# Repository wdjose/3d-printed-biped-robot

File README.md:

# 3D-Printed Biped Robot
This repository contains the 3D model and the source code for the 3D-printed biped robot presented in the conference: 

> [W. J. D. Jose and M. C. Ramos, "Development of a 3D-printed biped robot with distributed joint control," 2018 4th International Conference on Control, Automation and Robotics (ICCAR), Auckland, 2018, pp. 71-75.](https://ieeexplore.ieee.org/document/8384647/ "Development of a 3D-printed biped robot with distributed joint control")

The biped robot was designed from scratch: all mechanical, electronic, and control designs were built by the authors. 

Below are descriptions of the directories in the repository: 
1. 3D Model: This contains the SolidWorks parts and assemblies which was 3D-printed and laser cut. 
2. PCB Schematic and Layout: This contains EAGLE schematic and layout files for both the master and joint controllers. 
3. Joint Controller: This is the MPLAB X project used for motor control for the joint controller. 
4. Master Controller: This is the MPLAB X project used for motion control of the biped for the master controller. 

Additional details can be provided upon request. 

This project was developed at Electrical and Electronics Engineering Institute, University of the Philippines Diliman.

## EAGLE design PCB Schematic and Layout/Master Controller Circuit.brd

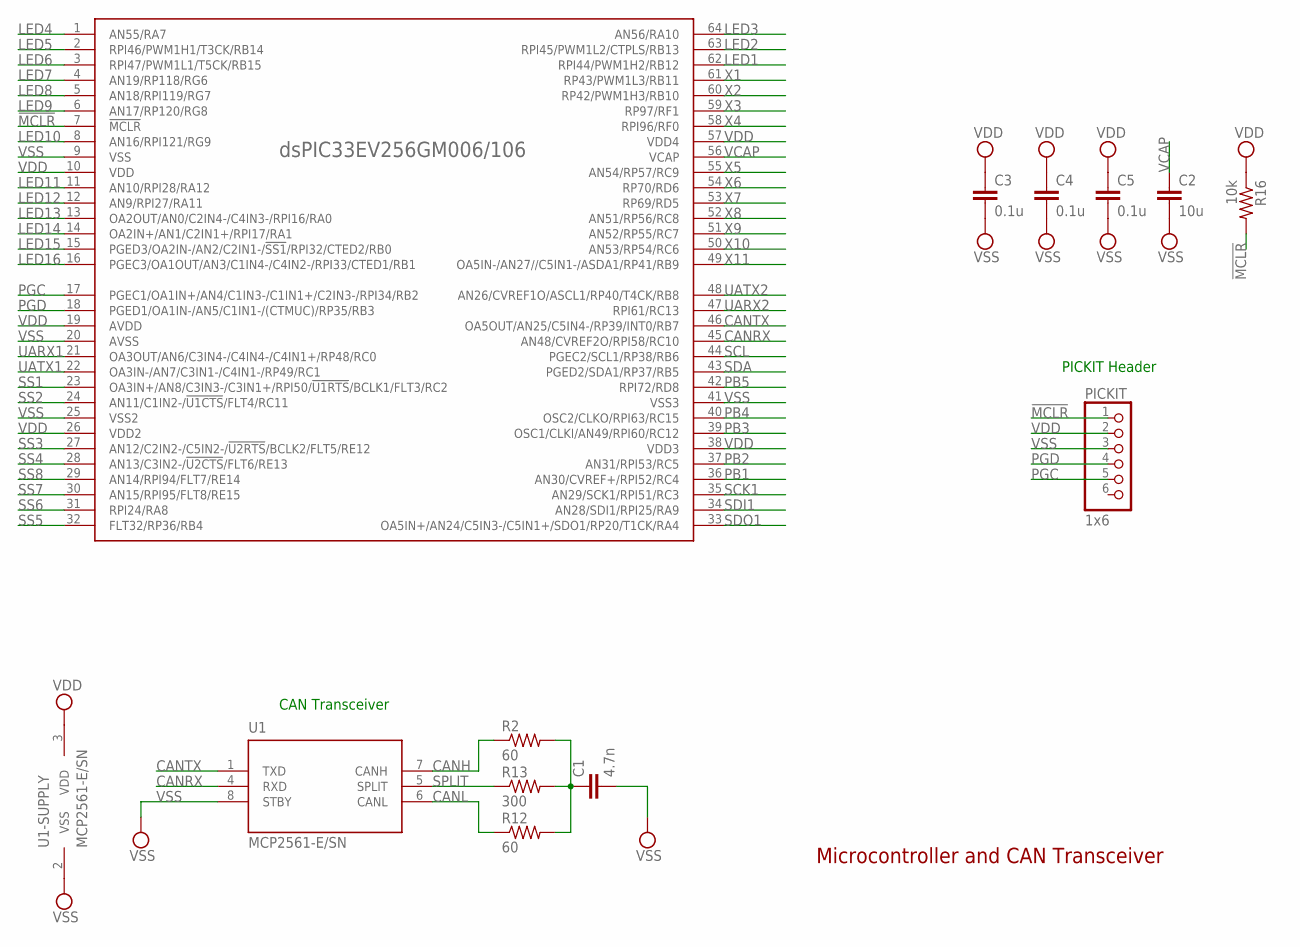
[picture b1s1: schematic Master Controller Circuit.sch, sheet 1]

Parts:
C1: 4.7n; C0805
C2: 10u; C0805
C3, C4, C5: 0.1u; C0805
PICKIT: 1x6; 1X06
R2, R12: 60; R0805
R13: 300; R0805
R16: 10k; R0805
U1: MCP2561-E/SN; SOIC-8
U$1: DSPIC33EV256GM106; TQFP64-10X10

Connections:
!MCLR: PICKIT.1, R16.2, U$1.7 (!MCLR); also elsewhere on the board
CANH: R2.1, U1.7 (CANH); also elsewhere on the board
CANL: R12.1, U1.6 (CANL); also elsewhere on the board
CANRX: U1.4 (RXD), U$1.45 (AN48/CVREF2O/RPI58/RC10)
CANTX: U1.1 (TXD), U$1.46 (OA5OUT/AN25/C5IN4-/RP39/INT0/RB7)
LED1: U$1.62 (RPI44/PWM1H2/RB12); also elsewhere on the board
LED2: U$1.63 (RPI45/PWM1L2/CTPLS/RB13); also elsewhere on the board
LED3: U$1.64 (AN56/RA10); also elsewhere on the board
LED4: U$1.1 (AN55/RA7); also elsewhere on the board
LED5: U$1.2 (RPI46/PWM1H1/T3CK/RB14); also elsewhere on the board
LED6: U$1.3 (RPI47/PWM1L1/T5CK/RB15); also elsewhere on the board
LED7: U$1.4 (AN19/RP118/RG6); also elsewhere on the board
LED8: U$1.5 (AN18/RPI119/RG7); also elsewhere on the board
LED9: U$1.6 (AN17/RP120/RG8); also elsewhere on the board
LED10: U$1.8 (AN16/RPI121/RG9); also elsewhere on the board
LED11: U$1.11 (AN10/RPI28/RA12); also elsewhere on the board
LED12: U$1.12 (AN9/RPI27/RA11); also elsewhere on the board
LED13: U$1.13 (OA2OUT/AN0/C2IN4-/C4IN3-/RPI16/RA0); also elsewhere on the board
LED14: U$1.14 (OA2IN+/AN1/C2IN1+/RPI17/RA1); also elsewhere on the board
LED15: U$1.15 (PGED3/OA2IN-/AN2/C2IN1-/!SS1!/RPI32/CTE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); also elsewhere on the board
LED16: U$1.16 (PGEC3/OA1OUT/AN3/C1IN4-/C4IN2-/RPI33/CT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); also elsewhere on the board
unnamed: C1.1, R2.2, R12.2, R13.2
PB1: U$1.36 (AN30/CVREF+/RPI52/RC4); also elsewhere on the board
PB2: U$1.37 (AN31/RPI53/RC5); also elsewhere on the board
PB3: U$1.39 (OSC1/CLKI/AN49/RPI60/RC12); also elsewhere on the board
PB4: U$1.40 (OSC2/CLKO/RPI63/RC15); also elsewhere on the board
PB5: U$1.42 (RPI72/RD8); also elsewhere on the board
PGC: PICKIT.5, U$1.17 (PGEC1/OA1IN+/AN4/C1IN3-/C1IN1+/C2IN3-/R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)
PGD: PICKIT.4, U$1.18 (PGED1/OA1IN-/AN5/C1IN1-/(CTMUC)/RP35/RB3)
SCK1: U$1.35 (AN29/SCK1/RPI51/RC3); also elsewhere on the board
SCL: U$1.44 (PGEC2/SCL1/RP38/RB6); also elsewhere on the board
SDA: U$1.43 (PGED2/SDA1/RP37/RB5); also elsewhere on the board
SDI1: U$1.34 (AN28/SDI1/RPI25/RA9); also elsewhere on the board
SDO1: U$1.33 (OA5IN+/AN24/C5IN3-/C5IN1+/SDO1/RP20/T1C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); also elsewhere on the board
SPLIT: R13.1, U1.5 (SPLIT)
SS1: U$1.23 (OA3IN+/AN8/C3IN3-/C3IN1+/RPI50/!U1RTS!/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); also elsewhere on the board
SS2: U$1.24 (AN11/C1IN2-/!U1CTS!/FLT4/RC11); also elsewhere on the board
SS3: U$1.27 (AN12/C2IN2-/C5IN2-/!U2RTS!/BCLK2/FLT5/R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); also elsewhere on the board
SS4: U$1.28 (AN13/C3IN2-/!U2CTS!/FLT6/RE13); also elsewhere on the board
SS5: U$1.32 (FLT32/RP36/RB4); also elsewhere on the board
SS6: U$1.31 (RPI24/RA8); also elsewhere on the board
SS7: U$1.30 (AN15/RPI95/FLT8/RE15); also elsewhere on the board
SS8: U$1.29 (AN14/RPI94/FLT7/RE14); also elsewhere on the board
UARX1: U$1.21 (OA3OUT/AN6/C3IN4-/C4IN4-/C4IN1+/RP48/RC0); also elsewhere on the board
UARX2: U$1.47 (RPI61/RC13); also elsewhere on the board
UATX1: U$1.22 (OA3IN-/AN7/C3IN1-/C4IN1-/RP49/RC1); also elsewhere on the board
UATX2: U$1.48 (AN26/CVREF1O/ASCL1/RP40/T4CK/RB8); also elsewhere on the board
VCAP: C2.1, U$1.56 (VCAP)
VDD: C3.1, C4.1, C5.1, PICKIT.2, R16.1, U1.3 (VDD), U$1.10 (VDD), U$1.19 (AVDD), U$1.26 (VDD2), U$1.38 (VDD3), U$1.57 (VDD4); also elsewhere on the board
VSS: C1.2, C2.2, C3.2, C4.2, C5.2, PICKIT.3, U1.2 (VSS), U1.8 (STBY), U$1.9 (VSS), U$1.20 (AVSS), U$1.25 (VSS2), U$1.41 (VSS3); also elsewhere on the board
X1: U$1.61 (RP43/PWM1L3/RB11); also elsewhere on the board
X2: U$1.60 (RP42/PWM1H3/RB10); also elsewhere on the board
X3: U$1.59 (RP97/RF1); also elsewhere on the board
X4: U$1.58 (RPI96/RF0); also elsewhere on the board
X5: U$1.55 (AN54/RP57/RC9); also elsewhere on the board
X6: U$1.54 (RP70/RD6); also elsewhere on the board
X7: U$1.53 (RP69/RD5); also elsewhere on the board
X8: U$1.52 (AN51/RP56/RC8); also elsewhere on the board
X9: U$1.51 (AN52/RP55/RC7); also elsewhere on the board
X10: U$1.50 (AN53/RP54/RC6); also elsewhere on the board
X11: U$1.49 (OA5IN-/AN27//C5IN1-/ASDA1/RP41/RB9); also elsewhere on the board

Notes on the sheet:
PICKIT Header
CAN Transceiver
Microcontroller and CAN Transceiver

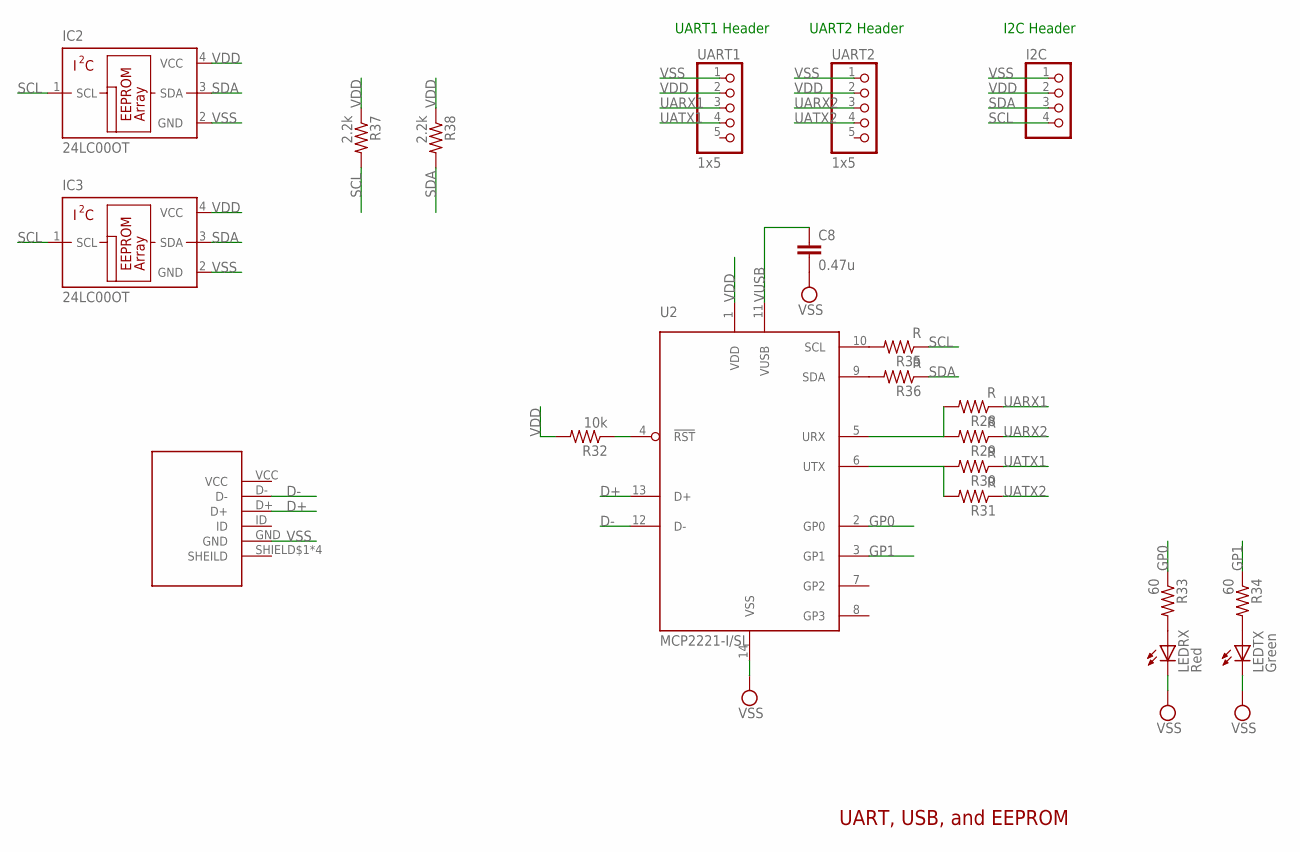
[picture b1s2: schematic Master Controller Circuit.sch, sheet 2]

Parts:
C8: 0.47u; C0805
I2C: PINHD-1X4; 1X04
IC2, IC3: 24LC00OT; SOT23-5L
J1: 10118193-0001LF
LEDRX: Red; CHIP-LED0805
LEDTX: Green; CHIP-LED0805
R28, R29, R30, R31, R35, R36: R; R0805
R32: 10k; R0805
R33, R34: 60; R0805
R37, R38: 2.2k; R0805
U2: MCP2221-I/SL; SOIC14
UART1, UART2: 1x5; 1X05

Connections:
D+: J1.D+, U2.13 (D+)
D-: J1.D-, U2.12 (D-)
GP0: R33.1, U2.2 (GP0)
GP1: R34.1, U2.3 (GP1)
unnamed: R28.2, R29.2, U2.5 (URX)
unnamed: R30.2, R31.2, U2.6 (UTX)
unnamed: R35.2, U2.10 (SCL)
unnamed: R36.2, U2.9 (SDA)
unnamed: R32.1, U2.4 (!RST)
unnamed: LEDRX.A, R33.2
unnamed: LEDTX.A, R34.2
SCL: I2C.4, IC2.1 (SCL), IC3.1 (SCL), R35.1, R37.2; also elsewhere on the board
SDA: I2C.3, IC2.3 (SDA), IC3.3 (SDA), R36.1, R38.2; also elsewhere on the board
UARX1: R28.1, UART1.3; also elsewhere on the board
UARX2: R29.1, UART2.3; also elsewhere on the board
UATX1: R30.1, UART1.4; also elsewhere on the board
UATX2: R31.1, UART2.4; also elsewhere on the board
VDD: I2C.2, IC2.4 (VCC), IC3.4 (VCC), R32.2, R37.1, R38.1, U2.1 (VDD), UART1.2, UART2.2; also elsewhere on the board
VSS: C8.2, I2C.1, IC2.2 (GND), IC3.2 (GND), J1.GND, LEDRX.C, LEDTX.C, U2.14 (VSS), UART1.1, UART2.1; also elsewhere on the board
VUSB: C8.1, U2.11 (VUSB)

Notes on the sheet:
UART, USB, and EEPROM
UART1 Header
UART2 Header
I2C Header

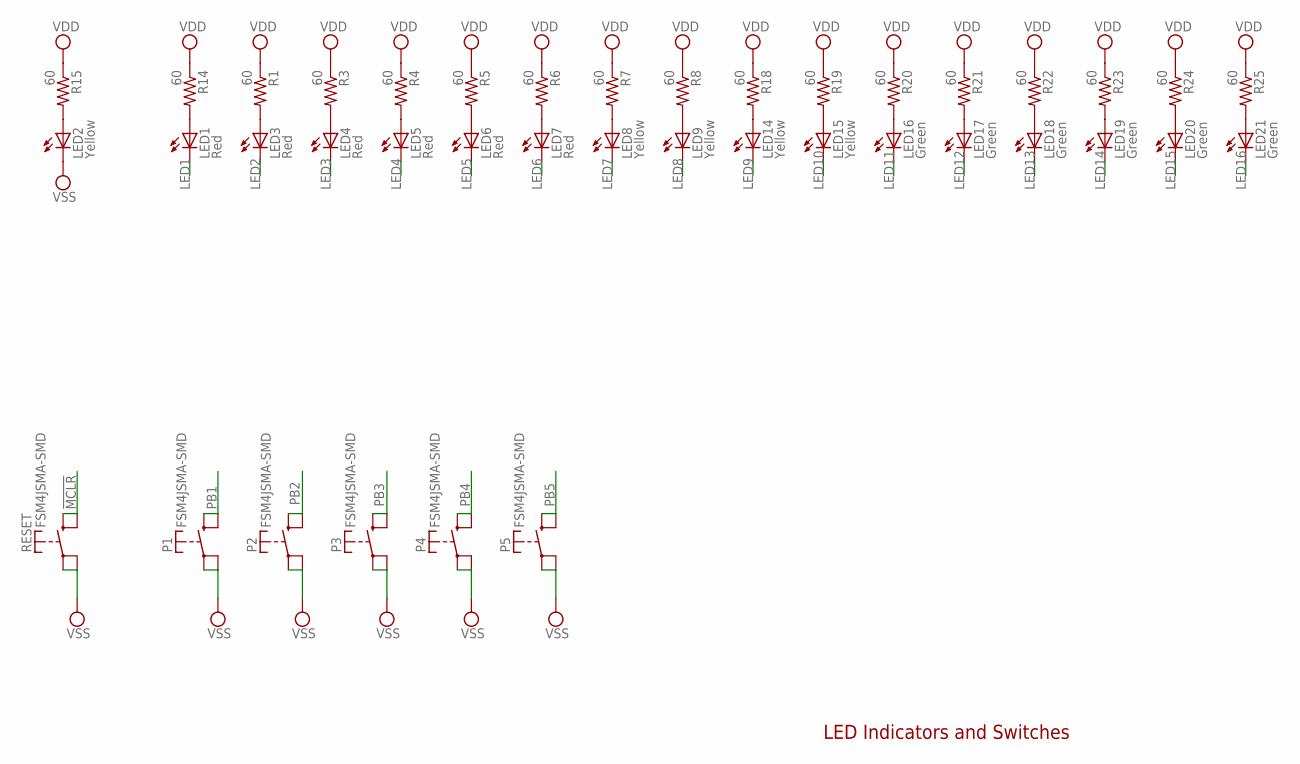
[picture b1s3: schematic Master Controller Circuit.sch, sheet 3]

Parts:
LED1, LED3, LED4, LED5, LED6, LED7: Red; CHIP-LED0805
LED2, LED8, LED9, LED14, LED15: Yellow; CHIP-LED0805
LED16, LED17, LED18, LED19, LED20, LED21: Green; CHIP-LED0805
P1, P2, P3, P4, P5: FSM4JSMA-SMD
R1, R3, R4, R5, R6, R7, R8, R14, R15, R18, R19, R20, R21, R22, R23, R24, R25: 60; R0805
RESET: FSM4JSMA-SMD

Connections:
!MCLR: RESET.P$3 (S), RESET.P$4 (S); also elsewhere on the board
LED1: LED1.C; also elsewhere on the board
LED2: LED3.C; also elsewhere on the board
LED3: LED4.C; also elsewhere on the board
LED4: LED5.C; also elsewhere on the board
LED5: LED6.C; also elsewhere on the board
LED6: LED7.C; also elsewhere on the board
LED7: LED8.C; also elsewhere on the board
LED8: LED9.C; also elsewhere on the board
LED9: LED14.C; also elsewhere on the board
LED10: LED15.C; also elsewhere on the board
LED11: LED16.C; also elsewhere on the board
LED12: LED17.C; also elsewhere on the board
LED13: LED18.C; also elsewhere on the board
LED14: LED19.C; also elsewhere on the board
LED15: LED20.C; also elsewhere on the board
LED16: LED21.C; also elsewhere on the board
unnamed: LED1.A, R14.2
unnamed: LED2.A, R15.2
unnamed: LED3.A, R1.2
unnamed: LED4.A, R3.2
unnamed: LED5.A, R4.2
unnamed: LED6.A, R5.2
unnamed: LED7.A, R6.2
unnamed: LED8.A, R7.2
unnamed: LED9.A, R8.2
unnamed: LED14.A, R18.2
unnamed: LED15.A, R19.2
unnamed: LED16.A, R20.2
unnamed: LED17.A, R21.2
unnamed: LED18.A, R22.2
unnamed: LED19.A, R23.2
unnamed: LED20.A, R24.2
unnamed: LED21.A, R25.2
PB1: P1.P$3 (S), P1.P$4 (S); also elsewhere on the board
PB2: P2.P$3 (S), P2.P$4 (S); also elsewhere on the board
PB3: P3.P$3 (S), P3.P$4 (S); also elsewhere on the board
PB4: P4.P$3 (S), P4.P$4 (S); also elsewhere on the board
PB5: P5.P$3 (S), P5.P$4 (S); also elsewhere on the board
VDD: R1.1, R3.1, R4.1, R5.1, R6.1, R7.1, R8.1, R14.1, R15.1, R18.1, R19.1, R20.1, R21.1, R22.1, R23.1, R24.1, R25.1; also elsewhere on the board
VSS: LED2.C, P1.P$1, P1.P$2, P2.P$1, P2.P$2, P3.P$1, P3.P$2, P4.P$1, P4.P$2, P5.P$1, P5.P$2, RESET.P$1, RESET.P$2; also elsewhere on the board

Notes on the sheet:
LED Indicators and Switches

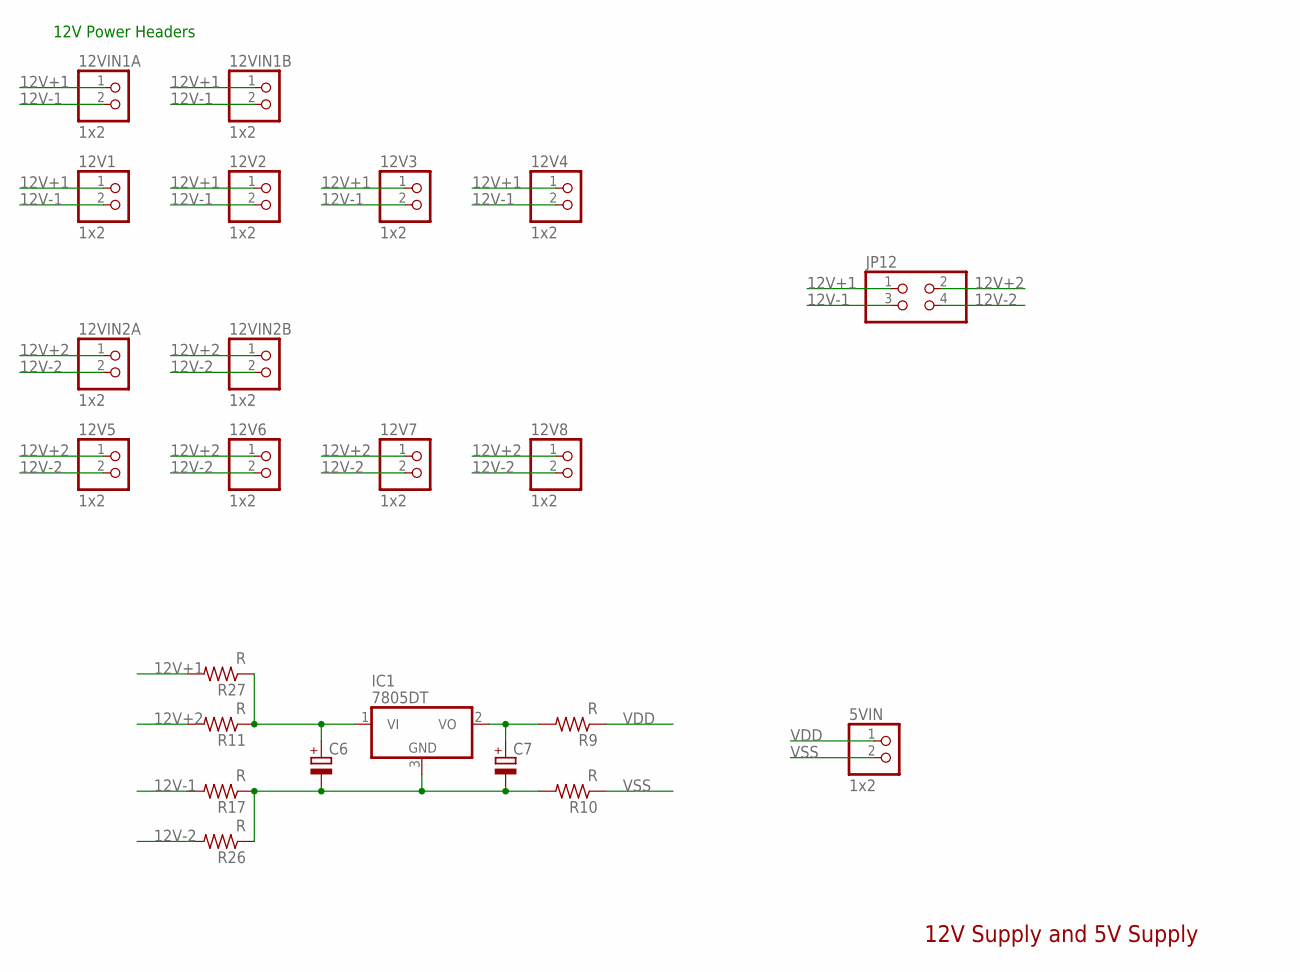
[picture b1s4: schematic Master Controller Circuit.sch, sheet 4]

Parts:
5VIN, 12V1, 12V2, 12V3, 12V4, 12V5, 12V6, 12V7, 12V8, 12VIN1A, 12VIN1B, 12VIN2A, 12VIN2B: 1x2; 1X02
C6, C7: CPOL-EU153CLV-0605; 153CLV-0605
IC1: 7805DT; TO252
JP12: PINHD-2X2; 2X02
R9, R10, R11, R17, R26, R27: R; R0805

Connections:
12V+1: 12V1.1, 12V2.1, 12V3.1, 12V4.1, 12VIN1A.1, 12VIN1B.1, JP12.1, R27.2
12V+2: 12V5.1, 12V6.1, 12V7.1, 12V8.1, 12VIN2A.1, 12VIN2B.1, JP12.2, R11.2
12V-1: 12V1.2, 12V2.2, 12V3.2, 12V4.2, 12VIN1A.2, 12VIN1B.2, JP12.3, R17.2
12V-2: 12V5.2, 12V6.2, 12V7.2, 12V8.2, 12VIN2A.2, 12VIN2B.2, JP12.4, R26.2
unnamed: C7.+, IC1.2 (VO), R9.2
unnamed: C6.-, C7.-, IC1.3 (GND), R10.2, R17.1, R26.1
unnamed: C6.+, IC1.1 (VI), R11.1, R27.1
VDD: 5VIN.1, R9.1; also elsewhere on the board
VSS: 5VIN.2, R10.1; also elsewhere on the board

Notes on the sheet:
12V Supply and 5V Supply
12V Power Headers

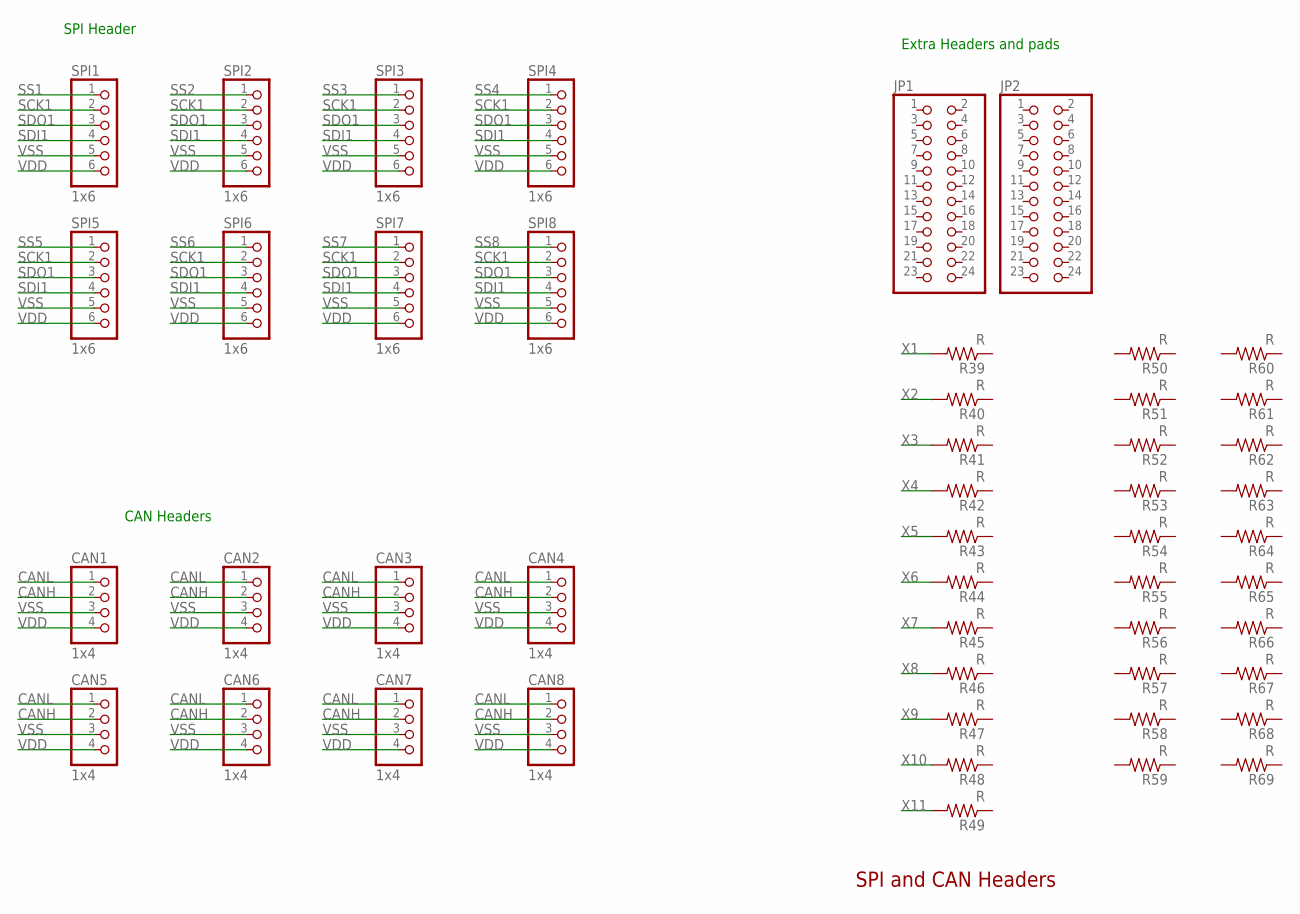
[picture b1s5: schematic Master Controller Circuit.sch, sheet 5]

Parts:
CAN1, CAN2, CAN3, CAN4, CAN5, CAN6, CAN7, CAN8: 1x4; 1X04
JP1, JP2: PINHD-2X12; 2X12
R39, R40, R41, R42, R43, R44, R45, R46, R47, R48, R49, R50, R51, R52, R53, R54, R55, R56, R57, R58, R59, R60, R61, R62, R63, R64, R65, R66, R67, R68, R69: R; R0603
SPI1, SPI2, SPI3, SPI4, SPI5, SPI6, SPI7, SPI8: 1x6; 1X06

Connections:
CANH: CAN1.2, CAN2.2, CAN3.2, CAN4.2, CAN5.2, CAN6.2, CAN7.2, CAN8.2; also elsewhere on the board
CANL: CAN1.1, CAN2.1, CAN3.1, CAN4.1, CAN5.1, CAN6.1, CAN7.1, CAN8.1; also elsewhere on the board
SCK1: SPI1.2, SPI2.2, SPI3.2, SPI4.2, SPI5.2, SPI6.2, SPI7.2, SPI8.2; also elsewhere on the board
SDI1: SPI1.4, SPI2.4, SPI3.4, SPI4.4, SPI5.4, SPI6.4, SPI7.4, SPI8.4; also elsewhere on the board
SDO1: SPI1.3, SPI2.3, SPI3.3, SPI4.3, SPI5.3, SPI6.3, SPI7.3, SPI8.3; also elsewhere on the board
SS1: SPI1.1; also elsewhere on the board
SS2: SPI2.1; also elsewhere on the board
SS3: SPI3.1; also elsewhere on the board
SS4: SPI4.1; also elsewhere on the board
SS5: SPI5.1; also elsewhere on the board
SS6: SPI6.1; also elsewhere on the board
SS7: SPI7.1; also elsewhere on the board
SS8: SPI8.1; also elsewhere on the board
VDD: CAN1.4, CAN2.4, CAN3.4, CAN4.4, CAN5.4, CAN6.4, CAN7.4, CAN8.4, SPI1.6, SPI2.6, SPI3.6, SPI4.6, SPI5.6, SPI6.6, SPI7.6, SPI8.6; also elsewhere on the board
VSS: CAN1.3, CAN2.3, CAN3.3, CAN4.3, CAN5.3, CAN6.3, CAN7.3, CAN8.3, SPI1.5, SPI2.5, SPI3.5, SPI4.5, SPI5.5, SPI6.5, SPI7.5, SPI8.5; also elsewhere on the board
X1: R39.2; also elsewhere on the board
X2: R40.2; also elsewhere on the board
X3: R41.2; also elsewhere on the board
X4: R42.2; also elsewhere on the board
X5: R43.2; also elsewhere on the board
X6: R44.2; also elsewhere on the board
X7: R45.2; also elsewhere on the board
X8: R46.2; also elsewhere on the board
X9: R47.2; also elsewhere on the board
X10: R48.2; also elsewhere on the board
X11: R49.2; also elsewhere on the board

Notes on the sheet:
SPI and CAN Headers
SPI Header
CAN Headers
Extra Headers and pads

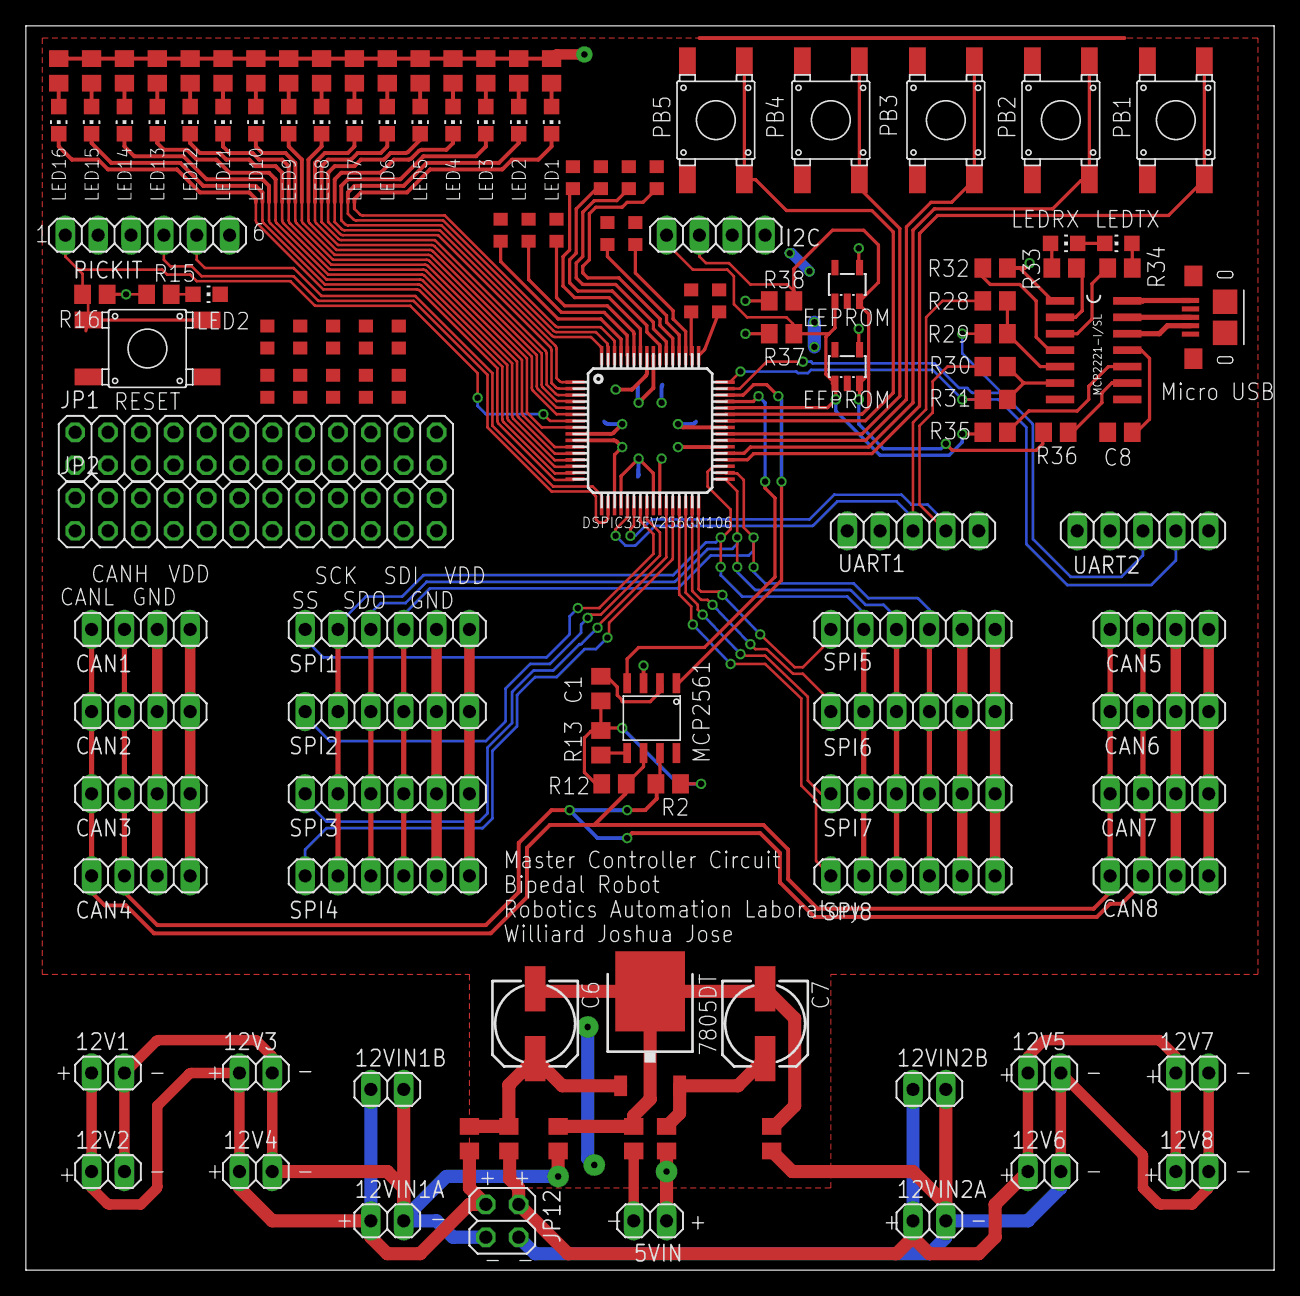
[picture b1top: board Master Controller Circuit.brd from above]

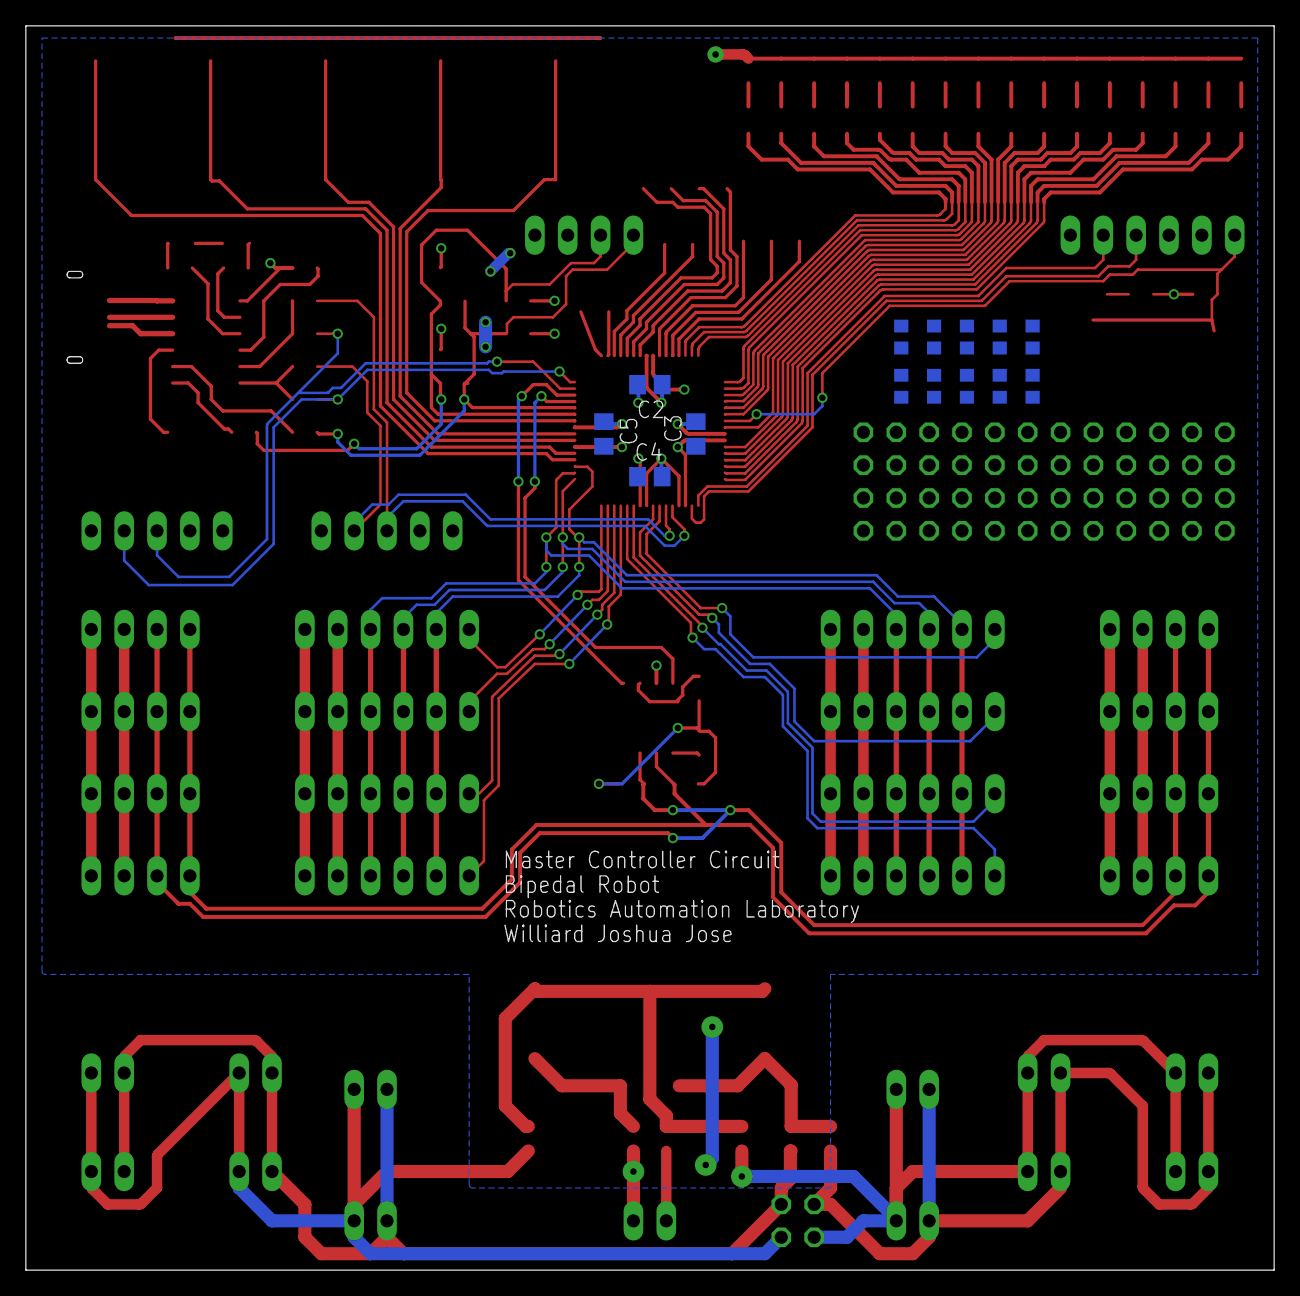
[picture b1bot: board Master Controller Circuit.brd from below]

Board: 2 copper layers, 96.5 x 96.2 mm, 145 parts (14 on the bottom side), 97 nets.

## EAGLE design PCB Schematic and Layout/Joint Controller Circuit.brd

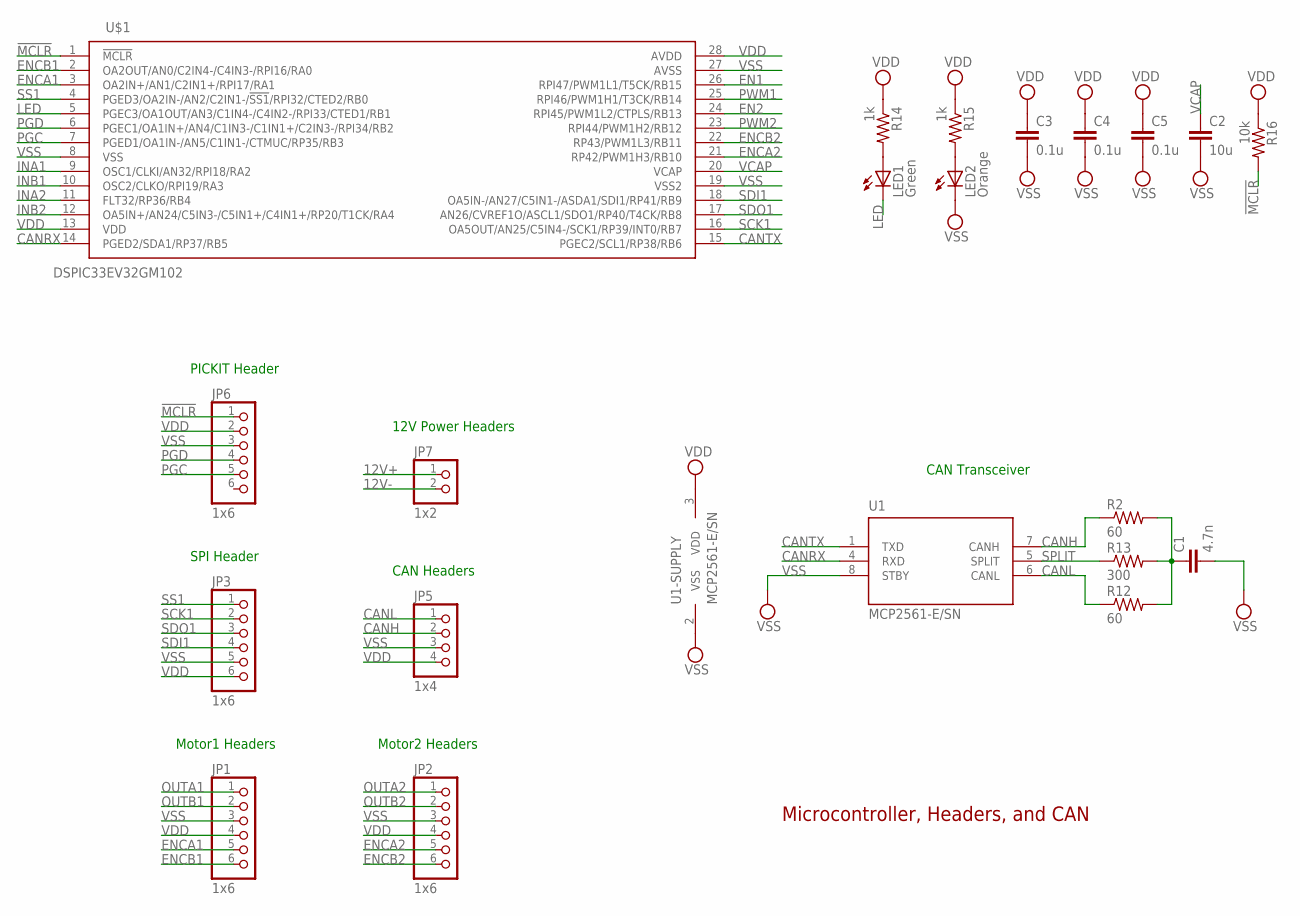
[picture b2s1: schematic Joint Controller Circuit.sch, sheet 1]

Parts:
C1: 4.7n; C0805
C2: 10u; C0805
C3, C4, C5: 0.1u; C0805
JP1, JP2, JP3, JP6: 1x6; 1X06
JP5: 1x4; 1X04
JP7: 1x2; 1X02
LED1: Green; CHIP-LED0805
LED2: Orange; CHIP-LED0805
R2, R12: 60; R0805
R13: 300; R0805
R14, R15: 1k; R0805
R16: 10k; R0805
U1: MCP2561-E/SN; SOIC-8
U$1: DSPIC33EV32GM102; SOIC28

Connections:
12V+: JP7.1; also elsewhere on the board
12V-: JP7.2; also elsewhere on the board
!MCLR: JP6.1, R16.2, U$1.1 (!MCLR)
CANH: JP5.2, R2.1, U1.7 (CANH)
CANL: JP5.1, R12.1, U1.6 (CANL)
CANRX: U1.4 (RXD), U$1.14 (PGED2/SDA1/RP37/RB5)
CANTX: U1.1 (TXD), U$1.15 (PGEC2/SCL1/RP38/RB6)
EN1: U$1.26 (RPI47/PWM1L1/T5CK/RB15); also elsewhere on the board
EN2: U$1.24 (RPI45/PWM1L2/CTPLS/RB13); also elsewhere on the board
ENCA1: JP1.5, U$1.3 (OA2IN+/AN1/C2IN1+/RPI17/RA1)
ENCA2: JP2.5, U$1.21 (RP42/PWM1H3/RB10)
ENCB1: JP1.6, U$1.2 (OA2OUT/AN0/C2IN4-/C4IN3-/RPI16/RA0)
ENCB2: JP2.6, U$1.22 (RP43/PWM1L3/RB11)
INA1: U$1.9 (OSC1/CLKI/AN32/RPI18/RA2); also elsewhere on the board
INA2: U$1.11 (FLT32/RP36/RB4); also elsewhere on the board
INB1: U$1.10 (OSC2/CLKO/RPI19/RA3); also elsewhere on the board
INB2: U$1.12 (OA5IN+/AN24/C5IN3-/C5IN1+/C4IN1+/RP20/T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); also elsewhere on the board
LED: LED1.C, U$1.5 (PGEC3/OA1OUT/AN3/C1IN4-/C4IN2-/RPI33/CT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)
unnamed: C1.1, R2.2, R12.2, R13.2
unnamed: LED1.A, R14.2
unnamed: LED2.A, R15.2
OUTA1: JP1.1; also elsewhere on the board
OUTA2: JP2.1; also elsewhere on the board
OUTB1: JP1.2; also elsewhere on the board
OUTB2: JP2.2; also elsewhere on the board
PGC: JP6.5, U$1.7 (PGED1/OA1IN-/AN5/C1IN1-/CTMUC/RP35/RB3)
PGD: JP6.4, U$1.6 (PGEC1/OA1IN+/AN4/C1IN3-/C1IN1+/C2IN3-/R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)
PWM1: U$1.25 (RPI46/PWM1H1/T3CK/RB14); also elsewhere on the board
PWM2: U$1.23 (RPI44/PWM1H2/RB12); also elsewhere on the board
SCK1: JP3.2, U$1.16 (OA5OUT/AN25/C5IN4-/SCK1/RP39/INT0/RB7)
SDI1: JP3.4, U$1.18 (OA5IN-/AN27/C5IN1-/ASDA1/SDI1/RP41/RB9)
SDO1: JP3.3, U$1.17 (AN26/CVREF1O/ASCL1/SDO1/RP40/T4CK/RB8)
SPLIT: R13.1, U1.5 (SPLIT)
SS1: JP3.1, U$1.4 (PGED3/OA2IN-/AN2/C2IN1-/!SS1!/RPI32/CTE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)
VCAP: C2.1, U$1.20 (VCAP)
VDD: C3.1, C4.1, C5.1, JP1.4, JP2.4, JP3.6, JP5.4, JP6.2, R14.1, R15.1, R16.1, U1.3 (VDD), U$1.13 (VDD), U$1.28 (AVDD); also elsewhere on the board
VSS: C1.2, C2.2, C3.2, C4.2, C5.2, JP1.3, JP2.3, JP3.5, JP5.3, JP6.3, LED2.C, U1.2 (VSS), U1.8 (STBY), U$1.8 (VSS), U$1.19 (VSS2), U$1.27 (AVSS); also elsewhere on the board

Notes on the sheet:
SPI Header
PICKIT Header
CAN Headers
12V Power Headers
Motor1 Headers
Motor2 Headers
CAN Transceiver
Microcontroller, Headers, and CAN

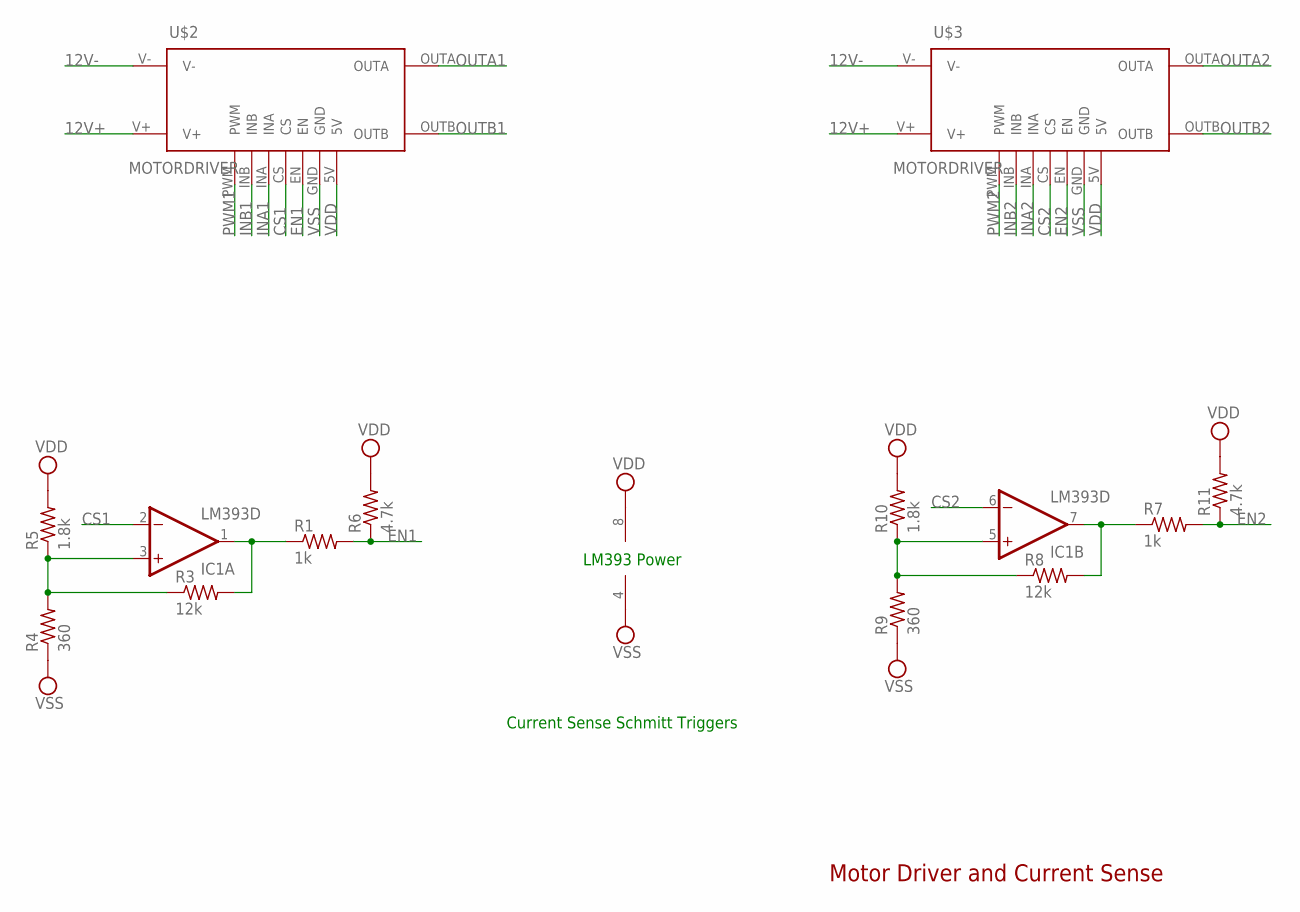
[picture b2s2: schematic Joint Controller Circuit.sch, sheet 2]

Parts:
IC1: LM393D; SO08
R1, R7: 1k; R0805
R3, R8: 12k; R0805
R4, R9: 360; R0805
R5, R10: 1.8k; R0805
R6, R11: 4.7k; R0805
U$2, U$3: MOTORDRIVER

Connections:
12V+: U$2.V+, U$3.V+; also elsewhere on the board
12V-: U$2.V-, U$3.V-; also elsewhere on the board
CS1: IC1.2 (-IN), U$2.CS
CS2: IC1.6 (-IN), U$3.CS
EN1: R1.2, R6.1, U$2.EN; also elsewhere on the board
EN2: R7.2, R11.1, U$3.EN; also elsewhere on the board
INA1: U$2.INA; also elsewhere on the board
INA2: U$3.INA; also elsewhere on the board
INB1: U$2.INB; also elsewhere on the board
INB2: U$3.INB; also elsewhere on the board
unnamed: IC1.7 (OUT), R7.1, R8.2
unnamed: IC1.5 (+IN), R8.1, R9.2, R10.1
unnamed: IC1.3 (+IN), R3.1, R4.2, R5.1
unnamed: IC1.1 (OUT), R1.1, R3.2
OUTA1: U$2.OUTA; also elsewhere on the board
OUTA2: U$3.OUTA; also elsewhere on the board
OUTB1: U$2.OUTB; also elsewhere on the board
OUTB2: U$3.OUTB; also elsewhere on the board
PWM1: U$2.PWM; also elsewhere on the board
PWM2: U$3.PWM; also elsewhere on the board
VDD: IC1.8 (V+), R5.2, R6.2, R10.2, R11.2, U$2.5V, U$3.5V; also elsewhere on the board
VSS: IC1.4 (V-), R4.1, R9.1, U$2.GND, U$3.GND; also elsewhere on the board

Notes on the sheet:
Current Sense Schmitt Triggers
LM393 Power
Motor Driver and Current Sense

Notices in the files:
parts and their libraries:
Volks73-MicrochipTechnology: Creative Commons Attribution-ShareAlike 3.0 Unported (CC BY-SA 3.0), http://creativecommons.org/licenses/by-sa/3.0/.
